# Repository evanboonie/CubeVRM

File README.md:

# CubeVRM
High power VRM for the Power Mac G4 Cube

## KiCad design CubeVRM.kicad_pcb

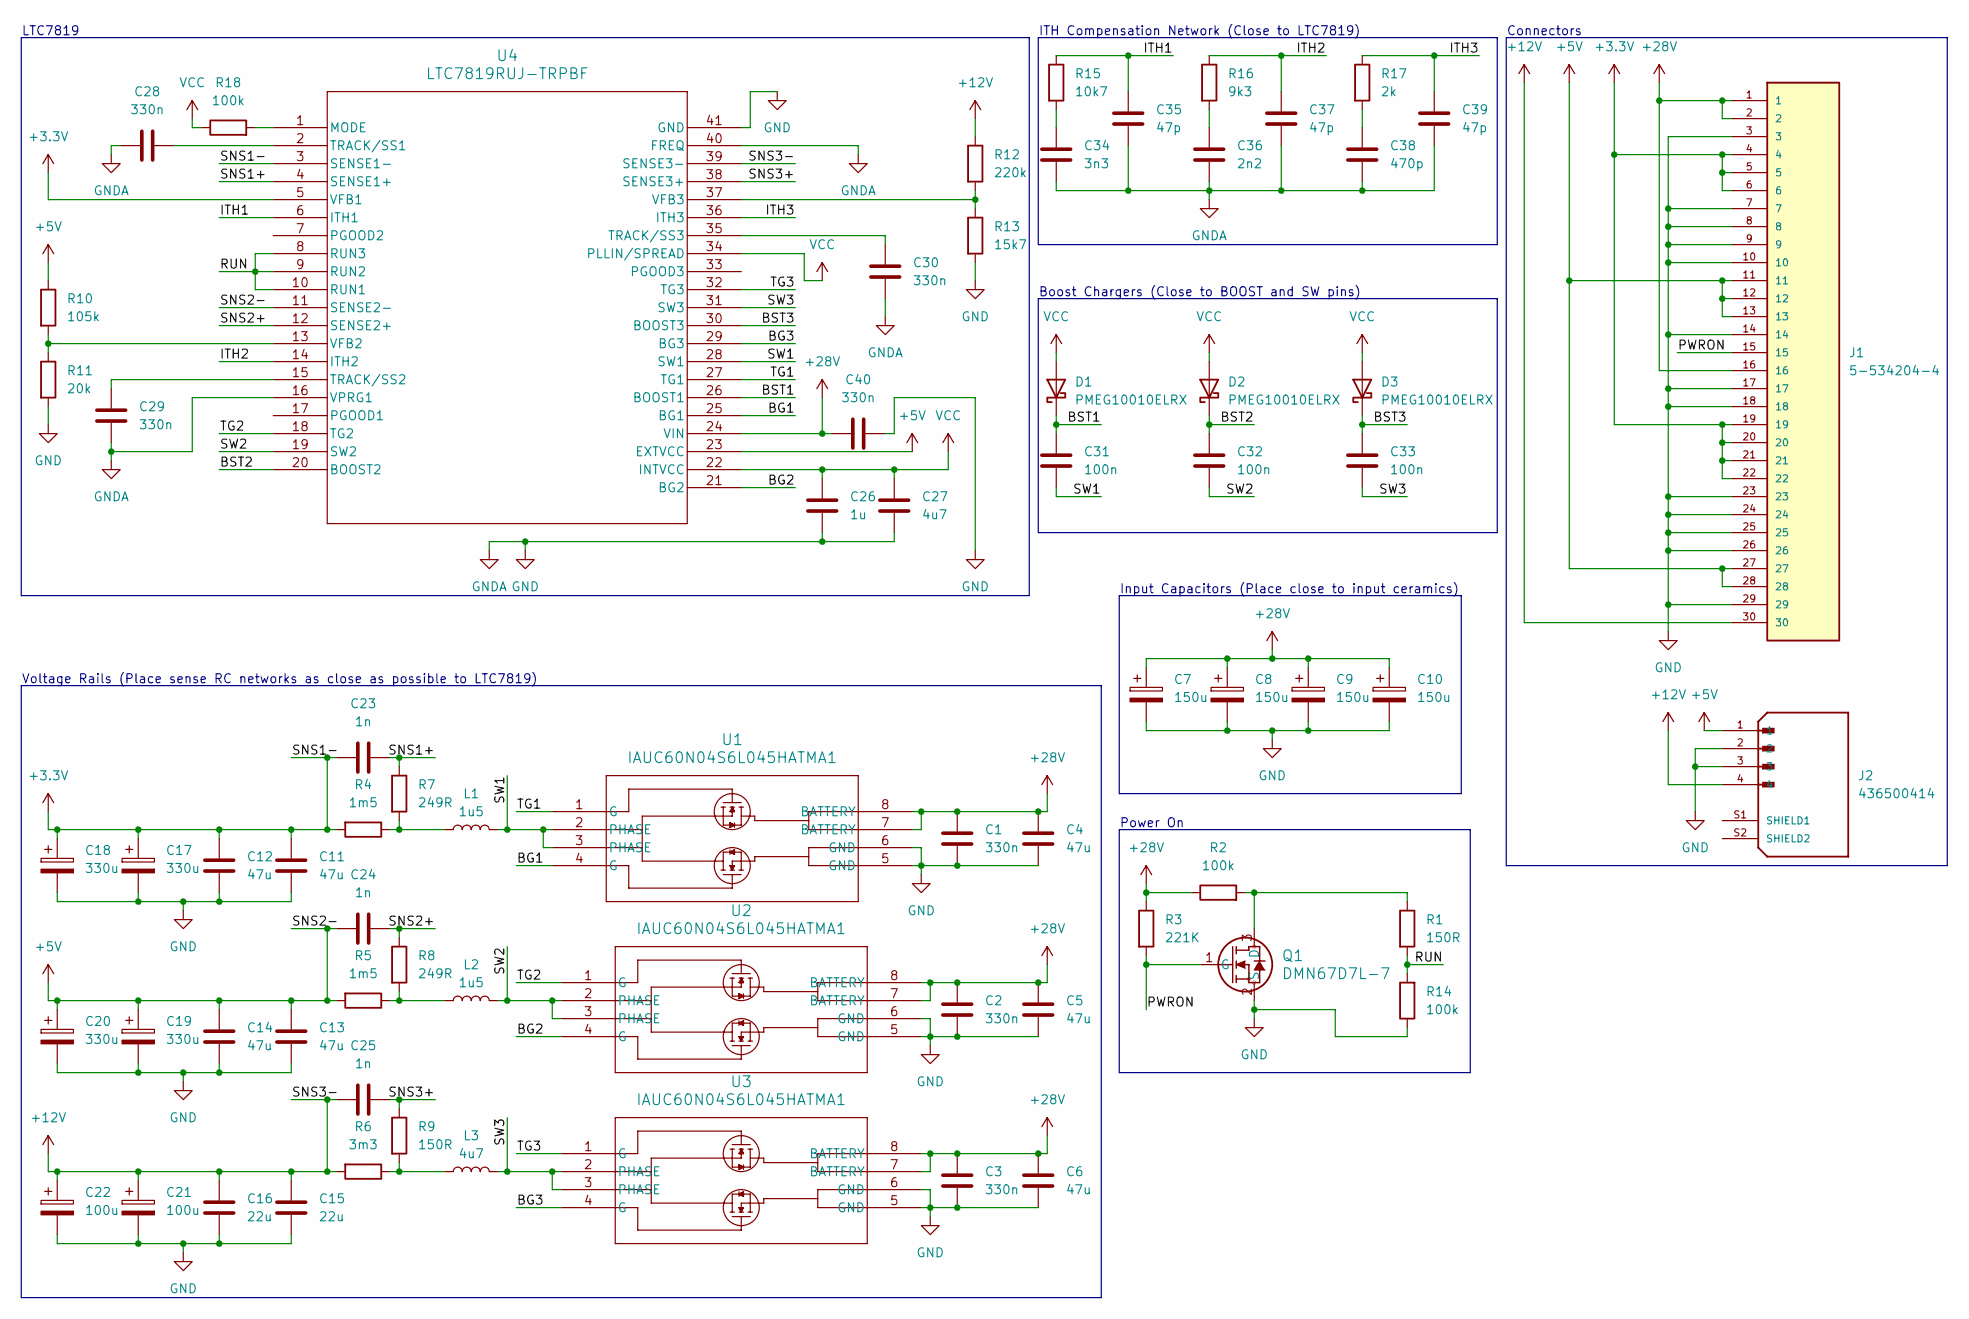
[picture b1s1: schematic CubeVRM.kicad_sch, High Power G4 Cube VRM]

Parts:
C1, C2, C3, C28, C29, C30, C40: 330n; C_0201_0603Metric
C4, C5, C6: 47u; C_2220_5650Metric
C7, C8, C9, C10: 150u; CAP_TCJ_U_KAV
C11, C12, C13, C14: 47u; C_1210_3225Metric
C15, C16: 22u; C_1210_3225Metric
C17, C18, C19, C20: 330u; CAP_ECGSY0J331R
C21, C22: 100u; CAP_ECGSY0J331R
C23, C24, C25: 1n; C_0603_1608Metric
C26: 1u; C_0603_1608Metric
C27: 4u7; C_0603_1608Metric
C31, C32, C33: 100n; C_0201_0603Metric
C34: 3n3; C_0201_0603Metric
C35, C37, C39: 47p; C_0201_0603Metric
C36: 2n2; C_0201_0603Metric
C38: 470p; C_0201_0603Metric
D1, D2, D3: PMEG10010ELRX; D_SOD-123
J1: 5-534204-4; TE_5-534204-4; PARTREV R; DigiKey_Part_Number A34325-ND
J2: 436500414; MOLEX_436500414; PARTREV E8; DigiKey_Part_Number WM3799TR-ND
L1, L2: 1u5; L_Bourns_SRP1245A
L3: 4u7; L_Bourns_SRP1245A
Q1: DMN67D7L-7; SOT23_DMN6_DIO
R1, R9: 150R; R_0603_1608Metric
R2, R14, R18: 100k; R_0603_1608Metric
R3: 221K; R_0603_1608Metric
R4, R5: 1m5; R_2512_6332Metric
R6: 3m3; R_2512_6332Metric
R7, R8: 249R; R_0603_1608Metric
R10: 105k; R_0603_1608Metric
R11: 20k; R_0603_1608Metric
R12: 220k; R_0603_1608Metric
R13: 15k7; R_0603_1608Metric
R15: 10k7; R_0603_1608Metric
R16: 9k3; R_0603_1608Metric
R17: 2k; R_0603_1608Metric
U1, U2, U3: IAUC60N04S6L045HATMA1; PG-TDSON-8-57
U4: LTC7819RUJ-TRPBF; 05-08-1728_ADI

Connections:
+3.3V: C11.1, C12.1, C17.1, C18.1, C23.1, J1.4, J1.5, J1.6, J1.19, J1.20, J1.21, J1.22, R4.2, U4.3 (SENSE1-), U4.5 (VFB1)
+5V: C13.1, C14.1, C19.1, C20.1, C24.1, J1.11, J1.12, J1.13, J1.27, J1.28, J2.1, R5.2, R10.1, U4.11 (SENSE2-), U4.23 (EXTVCC)
+12V: C15.1, C16.1, C21.1, C22.1, C25.1, J1.30, J2.4, R6.2, R12.1, U4.39 (SENSE3-)
+28V: C1.1, C2.1, C3.1, C4.1, C5.1, C6.1, C7.1, C8.1, C9.1, C10.1, C40.1, J1.1, J1.2, J1.16, R2.1, R3.1, U1.7 (BATTERY), U1.8 (BATTERY), U2.7 (BATTERY), U2.8 (BATTERY), U3.7 (BATTERY), U3.8 (BATTERY), U4.24 (VIN)
/BG1: U1.4 (G), U4.25 (BG1)
/BG2: U2.4 (G), U4.21 (BG2)
/BG3: U3.4 (G), U4.29 (BG3)
/BST1: C31.1, D1.1 (K), U4.26 (BOOST1)
/BST2: C32.1, D2.1 (K), U4.20 (BOOST2)
/BST3: C33.1, D3.1 (K), U4.30 (BOOST3)
/ITH1: C35.1, R15.1, U4.6 (ITH1)
/ITH2: C37.1, R16.1, U4.14 (ITH2)
/ITH3: C39.1, R17.1, U4.36 (ITH3)
/PWRON: J1.15, Q1.1 (G), R3.2
/RUN: R1.2, R14.2, U4.8 (RUN3), U4.9 (RUN2), U4.10 (RUN1)
/SNS1+: C23.2, R7.1, U4.4 (SENSE1+)
/SNS2+: C24.2, R8.1, U4.12 (SENSE2+)
/SNS3+: C25.2, R9.1, U4.38 (SENSE3+)
/SW1: C31.2, L1.2, U1.2 (PHASE), U1.3 (PHASE), U4.28 (SW1)
/SW2: C32.2, L2.2, U2.2 (PHASE), U2.3 (PHASE), U4.19 (SW2)
/SW3: C33.2, L3.2, U3.2 (PHASE), U3.3 (PHASE), U4.31 (SW3)
/TG1: U1.1 (G), U4.27 (TG1)
/TG2: U2.1 (G), U4.18 (TG2)
/TG3: U3.1 (G), U4.32 (TG3)
GND: C1.2, C2.2, C3.2, C4.2, C5.2, C6.2, C7.2, C8.2, C9.2, C10.2, C11.2, C12.2, C13.2, C14.2, C15.2, C16.2, C17.2, C18.2, C19.2, C20.2, C21.2, C22.2, C26.2, C27.2, C28.2, C29.1, C30.2, C34.2, C35.2, C36.2, C37.2, C38.2, C39.2, C40.2, J1.3, J1.7, J1.8, J1.9, J1.10, J1.14, J1.17, J1.18, J1.23, J1.24, J1.25, J1.26, J1.29, J2.2, J2.3, Q1.2 (S), R11.2, R13.2, R14.1, U1.5 (GND), U1.6 (GND), U2.5 (GND), U2.6 (GND), U3.5 (GND), U3.6 (GND), U4.16 (VPRG1), U4.40 (FREQ), U4.41 (GND)
unnamed: C34.1, R15.2
unnamed: C36.1, R16.2
unnamed: C38.1, R17.2
unnamed: L1.1, R4.1, R7.2
unnamed: L2.1, R5.1, R8.2
unnamed: L3.1, R6.1, R9.2
unnamed: Q1.3 (D), R1.1, R2.2
unnamed: R18.2, U4.1 (MODE)
unnamed: C28.1, U4.2 (TRACK/SS1)
unnamed: C29.2, U4.15 (TRACK/SS2)
unnamed: C30.1, U4.35 (TRACK/SS3)
unnamed: R10.2, R11.1, U4.13 (VFB2)
unnamed: R12.2, R13.1, U4.37 (VFB3)
VCC: C26.1, C27.1, D1.2 (A), D2.2 (A), D3.2 (A), R18.1, U4.22 (INTVCC), U4.34 (PLLIN/SPREAD)

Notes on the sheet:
ITH Compensation Network (Close to LTC7819)
Input Capacitors (Place close to input ceramics)
LTC7819
Voltage Rails (Place sense RC networks as close as possible to LTC7819)
Boost Chargers (Close to BOOST and SW pins)
Connectors
Power On

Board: 2 copper layers, 71 parts (0 on the bottom side), 39 nets, no tracks yet.

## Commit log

2023-10-02 initial
